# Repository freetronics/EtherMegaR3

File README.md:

Freetronics EtherMega R3
========================
Copyright 2011-2012 Freetronics Pty Ltd  
Freetronics site:  www.freetronics.com  
Freetronics email: info@freetronics.com  

The EtherMega R3 is a 100% Arduino-compatible board based on the existing
Mega2560, but with improvements and updates for features and ease of
use. It also includes on-board Ethernet with PoE (Power-over-Ethernet)
support.

Features:

 * High-efficiency switchmode power supply (input voltage 7-28Vdc)
 * Micro-USB Connector
 * microSD card slot
 * 10/100 Ethernet using the Wiznet W5100 chip
 * Overlay guide where you need it (both top and bottom)
 * D13 pin works for everything

You can view more at our product page at:

  http://www.freetronics.com/ethermega

INSTALLATION
------------
The design is saved as an EAGLE project. EAGLE PCB design software is
available from www.cadsoftusa.com free for non-commercial use. To use
this project download it and place the directory containing these files
into the "eagle" directory on your computer. Then open EAGLE and
navigate to Projects -> eagle -> EtherMegaR3.

DISTRIBUTION
------------
The specific terms of distribution of this project are governed by the
license referenced below.

LICENSE
-------
This work is licensed under the
Creative Commons Attribution-Share Alike License.  
To view a copy of this license, visit

  http://creativecommons.org/licenses/by-sa/3.0/  
  http://creativecommons.org/licenses/by-sa/3.0/legalcode

or send a letter to

  Creative Commons  
  171 Second Street, Suite 300  
  San Francisco  
  California, 94105  
  USA

The "license" folder within this repository also contains copies of the
licences referenced above.

CREDITS
-------
The EtherMega was designed by Marc Alexander (marc@freetronics.com) and
Jonathan Oxer (jon@freetronics.com) based on previous work by the Arduino
team (www.arduino.cc/playground/Main/People) which includes:

 * Massimo Banzi
 * David Cuartielles
 * Tom Igoe
 * Gianluca Martino
 * David A. Mellis

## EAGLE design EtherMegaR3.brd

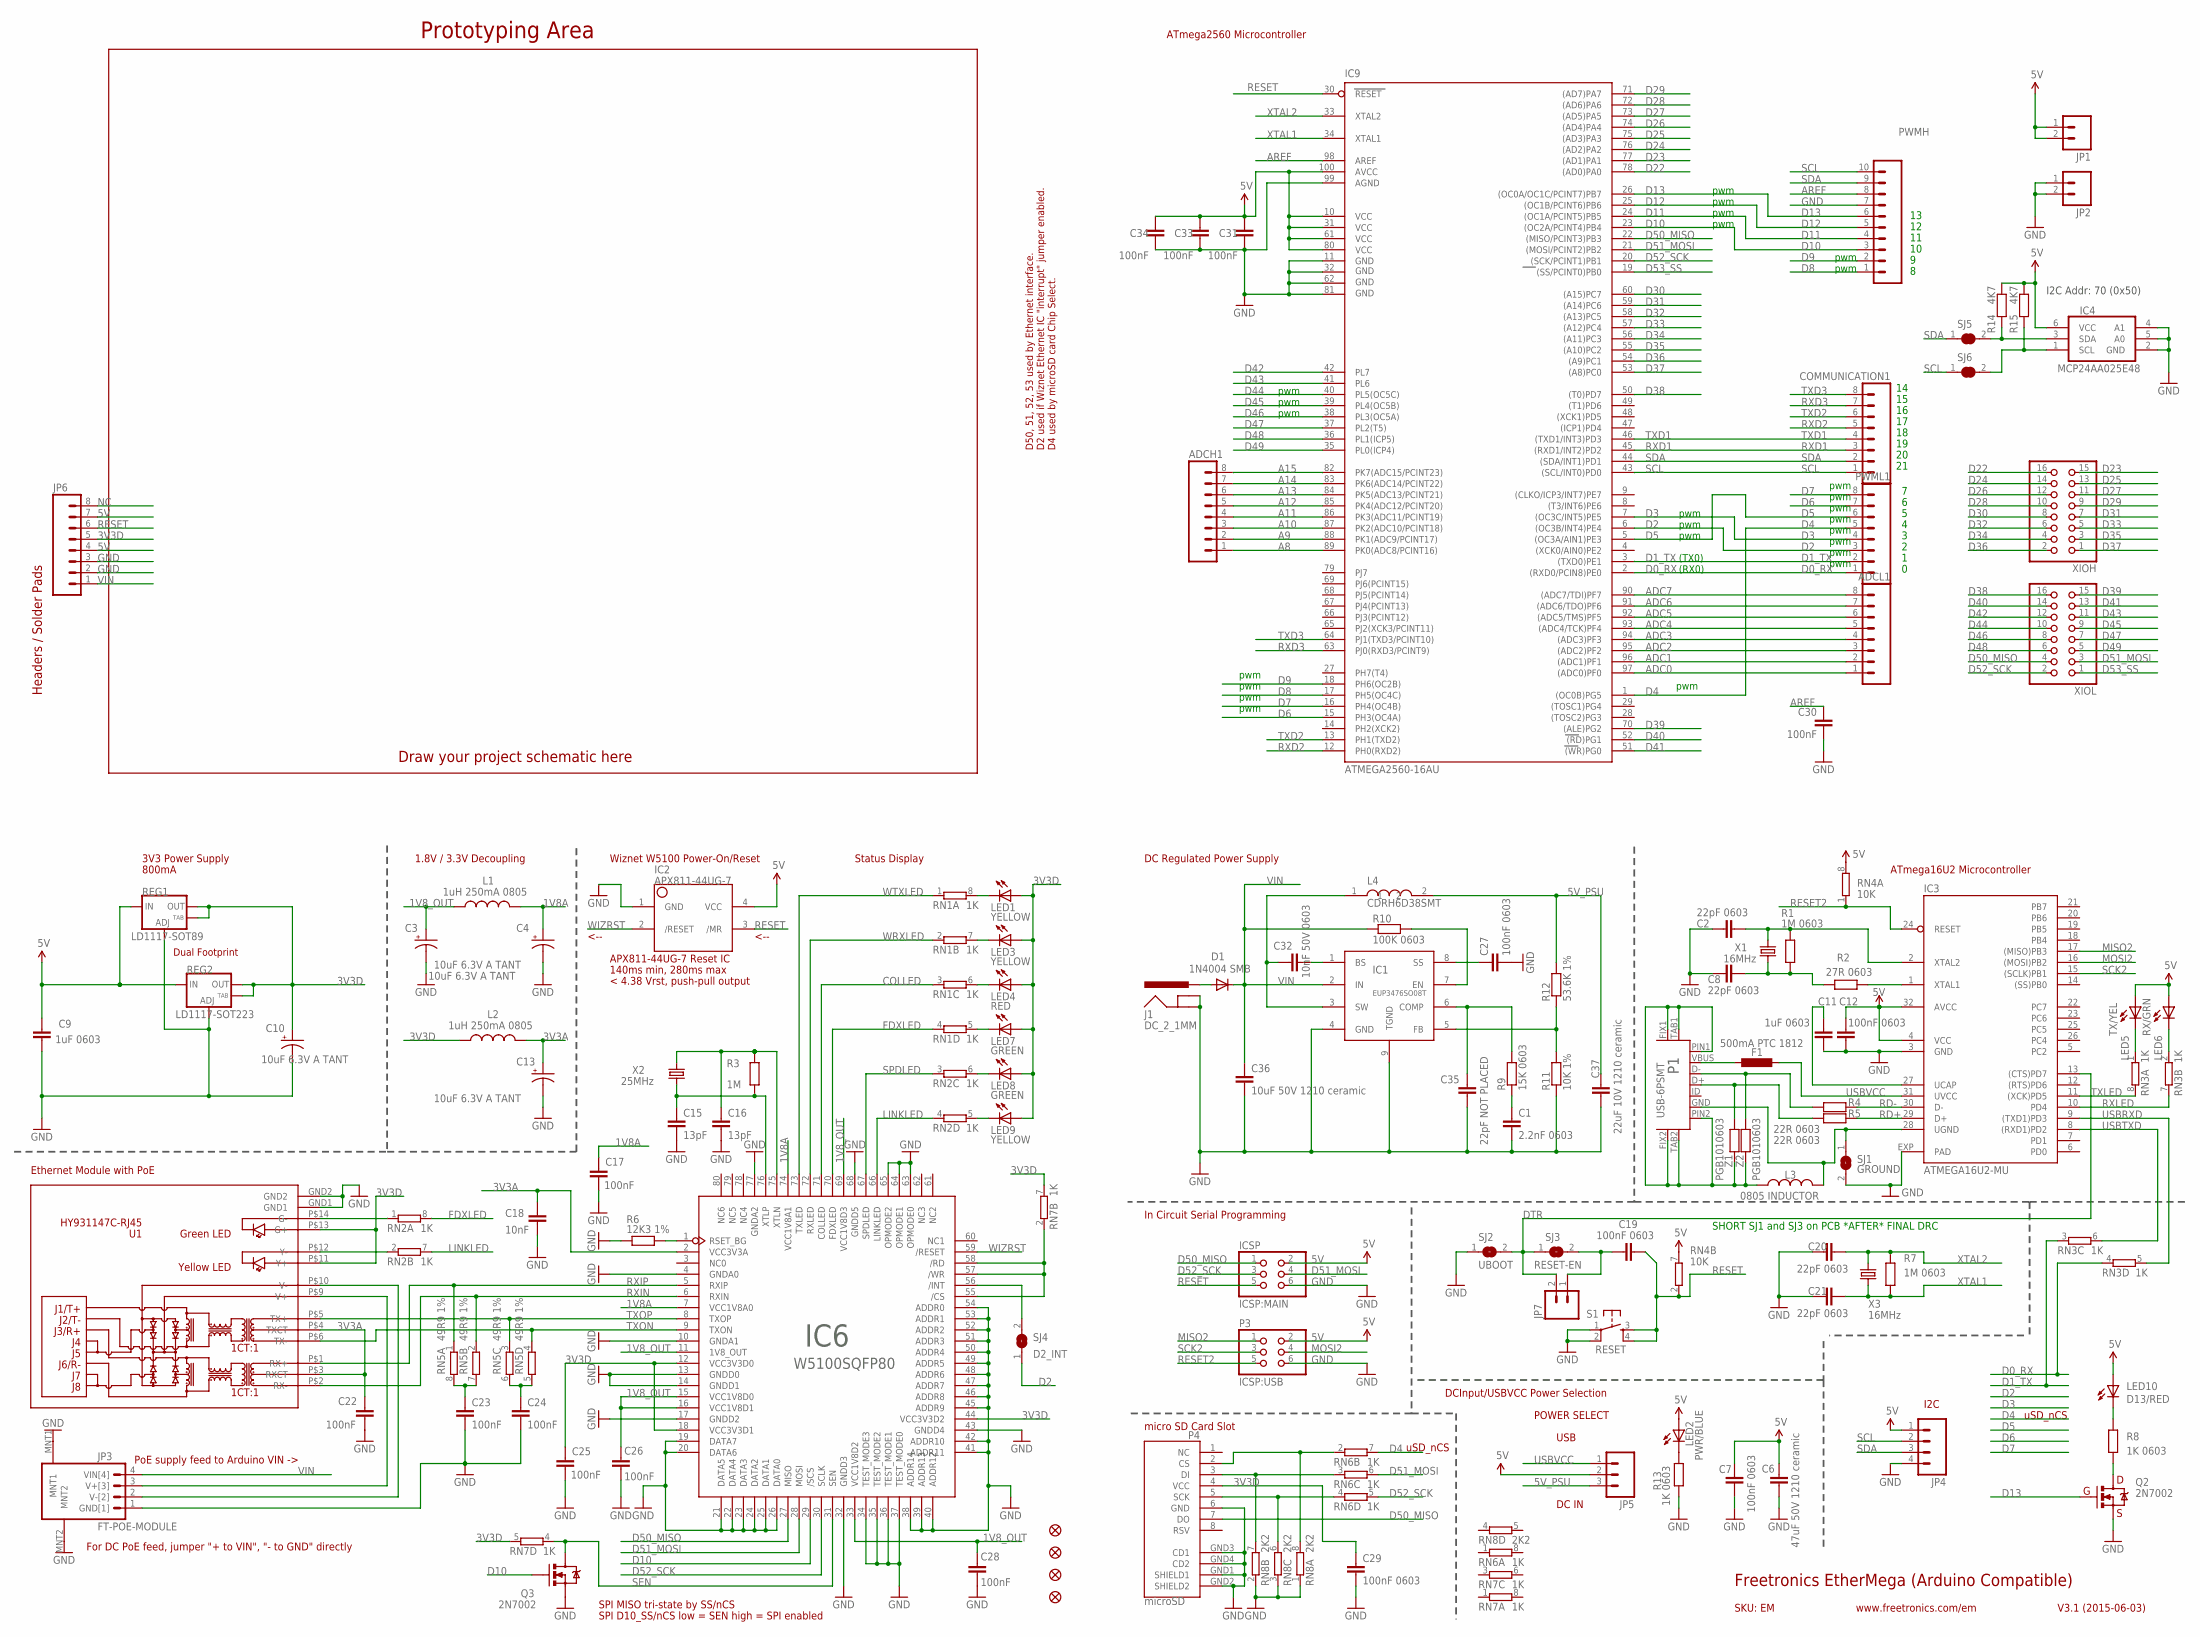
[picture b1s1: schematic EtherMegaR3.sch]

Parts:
ADCH1: M08STD; 1X08
ADCL1: M08STD; 1X08
C1: 2.2nF 0603; 0603
C2, C8, C20, C21: 22pF 0603; 0603
C3, C4, C10, C13: 10uF 6.3V A TANT; EIA3216
C6: 47uF 50V 1210 ceramic; C1210
C7, C12, C19, C27, C29: 100nF 0603; 0603
C9, C11: 1uF 0603; 0603
C15, C16: 13pF; 0603
C17, C22, C23, C24, C25, C26, C28, C30, C31, C33, C34: 100nF; 0603
C18: 10nF; 0603
C32: 10nF 50V 0603; 0603
C35: 22pF NOT PLACED; 0603
C36: 10uF 50V 1210 ceramic; C1210
C37: 22uF 10V 1210 ceramic; C1210
COMMUNICATION1: M08STD; 1X08
D1: 1N4004 SMB; SMB-DIODE
F1: 500mA PTC 1812; L1812
FID1, FID2, FID3, FID4: FIDUCIAL1X2.5; FIDUCIAL-1X2.5
IC1: EUP3476SO08T; SO08T
IC2: APX811-44UG-7; SOT143-R
IC3: ATMEGA16U2-MU; ATMEL_QFN32
IC4: MCP24AA025E48; SOT23-6
IC6: W5100SQFP80; SQFP80
IC9: ATMEGA2560-16AU; TQFP100
ICSP: ICSP:MAIN; 2X03
J1: DC_2_1MM; POWER_JACK_PTH
JP1, JP2, JP7: M02PTH; 1X02
JP3: FT-POE-MODULE; FT-POE-MODULE-CLEAN
JP4: M04PTH; 1X04
JP5: M03PTH; 1X03
JP6: M08STD; 1X08
L1, L2: 1uH 250mA 0805; L2012C
L3: 0805 INDUCTOR; 0805-LARGE
L4: CDRH6D38SMT; CDRH
LED1, LED3, LED9: YELLOW; LED-0603
LED2: PWR/BLUE; LED-0603
LED4: RED; LED-0603
LED5: TX/YEL; LED-0603
LED6: RX/GRN; LED-0603
LED7, LED8: GREEN; LED-0603
LED10: D13/RED; LED-0603
P1: USB-6PSMT; USB-MICROB-MB05PMXX
P3: ICSP:USB; 2X03
P4: microSD; MOLEX-SD-500901-003
PWMH: M100.1; 1X10
PWML1: M08STD; 1X08
Q2, Q3: 2N7002; SOT23-3
R1, R7: 1M 0603; 0603
R2: 27R 0603; 0603
R3: 1M; 0603
R4, R5: 22R 0603; 0603
R6: 12K3 1%; 0603
R8, R13: 1K 0603; 0603
R9: 15K 0603; 0603
R10: 100K 0603; 0603
R11: 10K 1%; 0603
R12: 53.6K 1%; 0603
R14, R15: 4K7; 0603
REG1: LD1117-SOT89; SOT89
REG2: LD1117-SOT223; SOT223
RN1, RN2, RN3, RN6, RN7: 1K; CAY16
RN4: 10K; CAY16
RN5: 49R9 1%; CAY16
RN8: 2K2; CAY16
S1: RESET; TACTILE_SWITCH_SMD
SJ1: GROUND; SJ
SJ2: UBOOT; SJ
SJ3: RESET-EN; SJ
SJ4: D2_INT; SJ
SJ5, SJ6: SJCN; SJC
U1: HY931147C-RJ45; HY931147C
X1, X3: 16MHz; HC49U-V
X2: 25MHz; HC49U-V
XIOH: PINHD-2X8; 2X08
XIOL: PINHD-2X8; 2X08
Z1, Z2: PGB1010603; 0603

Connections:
1V8A: C4.A (+), C17.1, IC6.7 (VCC1V8A0), IC6.74 (VCC1V8A1), L1.2
1V8_OUT: C3.A (+), C26.1, C28.1, IC6.11 (1V8_OUT), IC6.15 (VCC1V8D0), IC6.16 (VCC1V8D1), IC6.33 (VCC1V8D2), IC6.69 (VCC1V8D3), L1.1
3V3A: C13.A (+), C18.1, C22.1, IC6.2 (VCC3V3A), L2.2, U1.P$3 (RXCT), U1.P$4 (TXCT)
3V3D: C10.A (+), C25.1, C29.1, IC6.12 (VCC3V3D0), IC6.18 (VCC3V3D1), IC6.44 (VCC3V3D2), JP6.5, L2.1, LED1.A, LED3.A, LED4.A, LED7.A, LED8.A, LED9.A, P4.4 (VCC), REG1.2 (OUT), REG1.4 (OUT), REG2.2 (OUT), REG2.4 (OUT), RN7.5 (2), RN7.7 (2), U1.P$11 (Y+), U1.P$13 (G+)
5V: C6.2, C7.1, C9.1, C12.1, C31.1, C33.1, C34.1, IC2.4 (VCC), IC3.4 (VCC), IC3.32 (AVCC), IC4.6 (VCC), IC9.10 (VCC), IC9.31 (VCC1), IC9.61 (VCC2), IC9.80 (VCC3), IC9.100 (AVCC), ICSP.2, JP1.1, JP1.2, JP4.1, JP5.2, JP6.4, JP6.7, LED2.A, LED5.A, LED6.A, LED10.A, P3.2, R14.1, R15.1, REG1.3 (IN), REG2.3 (IN), RN4.7 (2), RN4.8 (2)
5V_PSU: C37.1, JP5.3, L4.2, R12.2
A8: ADCH1.1, IC9.89 (PK0(ADC8/PCINT16))
A9: ADCH1.2, IC9.88 (PK1(ADC9/PCINT17))
A10: ADCH1.3, IC9.87 (PK2(ADC10/PCINT18))
A11: ADCH1.4, IC9.86 (PK3(ADC11/PCINT19))
A12: ADCH1.5, IC9.85 (PK4(ADC12/PCINT20))
A13: ADCH1.6, IC9.84 (PK5(ADC13/PCINT21))
A14: ADCH1.7, IC9.83 (PK6(ADC14/PCINT22))
A15: ADCH1.8, IC9.82 (PK7(ADC15/PCINT23))
ADC0: ADCL1.1, IC9.97 ((ADC0)PF0)
ADC1: ADCL1.2, IC9.96 ((ADC1)PF1)
ADC2: ADCL1.3, IC9.95 ((ADC2)PF2)
ADC3: ADCL1.4, IC9.94 ((ADC3)PF3)
ADC4: ADCL1.5, IC9.93 ((ADC4/TCK)PF4)
ADC5: ADCL1.6, IC9.92 ((ADC5/TMS)PF5)
ADC6: ADCL1.7, IC9.91 ((ADC6/TDO)PF6)
ADC7: ADCL1.8, IC9.90 ((ADC7/TDI)PF7)
AREF: C30.1, IC9.98 (AREF), PWMH.8
COLLED: IC6.71 (COLLED), RN1.3 (1)
D0_RX: IC9.2 ((RXD0/PCIN8)PE0), PWML1.1, RN3.4 (1)
D1_TX: IC9.3 ((TXD0)PE1), PWML1.2, RN3.3 (1)
D2: IC9.6 ((OC3B/INT4)PE4), PWML1.3, SJ4.1
D3: IC9.7 ((OC3C/INT5)PE5), PWML1.4
D4: IC9.1 ((OC0B)PG5), PWML1.5, RN6.7 (2)
D5: IC9.5 ((OC3A/AIN1)PE3), PWML1.6
D6: IC9.15 (PH3(OC4A)), PWML1.7
D7: IC9.16 (PH4(OC4B)), PWML1.8
D8: IC9.17 (PH5(OC4C)), PWMH.1
D9: IC9.18 (PH6(OC2B)), PWMH.2
D10: IC6.29 (/SCS), IC9.23 ((OC2A/PCINT4)PB4), PWMH.3, Q3.1 (G)
D11: IC9.24 ((OC1A/PCINT5)PB5), PWMH.4
D12: IC9.25 ((OC1B/PCINT6)PB6), PWMH.5
D13: IC9.26 ((OC0A/OC1C/PCINT7)PB7), PWMH.6, Q2.1 (G)
D22: IC9.78 ((AD0)PA0), XIOH.16
D23: IC9.77 ((AD1)PA1), XIOH.15
D24: IC9.76 ((AD2)PA2), XIOH.14
D25: IC9.75 ((AD3)PA3), XIOH.13
D26: IC9.74 ((AD4)PA4), XIOH.12
D27: IC9.73 ((AD5)PA5), XIOH.11
D28: IC9.72 ((AD6)PA6), XIOH.10
D29: IC9.71 ((AD7)PA7), XIOH.9
D30: IC9.60 ((A15)PC7), XIOH.8
D31: IC9.59 ((A14)PC6), XIOH.7
D32: IC9.58 ((A13)PC5), XIOH.6
D33: IC9.57 ((A12)PC4), XIOH.5
D34: IC9.56 ((A11)PC3), XIOH.4
D35: IC9.55 ((A10)PC2), XIOH.3
D36: IC9.54 ((A9)PC1), XIOH.2
D37: IC9.53 ((A8)PC0), XIOH.1
D38: IC9.50 ((T0)PD7), XIOL.16
D39: IC9.70 ((ALE)PG2), XIOL.15
D40: IC9.52 ((RD)PG1), XIOL.14
D41: IC9.51 ((WR)PG0), XIOL.13
D42: IC9.42 (PL7), XIOL.12
D43: IC9.41 (PL6), XIOL.11
D44: IC9.40 (PL5(OC5C)), XIOL.10
D45: IC9.39 (PL4(OC5B)), XIOL.9
D46: IC9.38 (PL3(OC5A)), XIOL.8
D47: IC9.37 (PL2(T5)), XIOL.7
D48: IC9.36 (PL1(ICP5)), XIOL.6
D49: IC9.35 (PL0(ICP4)), XIOL.5
D50_MISO: IC6.27 (MISO), IC9.22 ((MISO/PCINT3)PB3), ICSP.1, P4.7 (DO), XIOL.4
D51_MOSI: IC6.28 (MOSI), IC9.21 ((MOSI/PCINT2)PB2), ICSP.4, RN6.6 (2), XIOL.3
D52_SCK: IC6.30 (SCLK), IC9.20 ((SCK/PCINT1)PB1), ICSP.3, RN6.5 (2), XIOL.2
D53_SS: IC9.19 ((SS/PCINT0)PB0), XIOL.1
DTR: IC3.13 ((CTS)PD7), JP7.2, SJ2.2, SJ3.1
FDXLED: IC6.70 (FDXLED), RN1.4 (1), RN2.8 (2)
GND: C1.2, C2.1, C3.C (-), C4.C (-), C6.1, C7.2, C8.1, C9.2, C10.C (-), C11.2, C12.2, C13.C (-), C15.2, C16.2, C17.2, C18.2, C20.1, C21.1, C22.2, C23.2, C24.2, C25.2, C26.2, C27.2, C28.2, C29.2, C30.2, C31.2, C33.2, C34.2, C35.2, C36.2, C37.2, IC1.4 (GND), IC1.9 (TGND), IC2.1 (GND), IC3.3 (GND), IC3.EXP (PAD), IC4.2 (GND), IC4.4 (A1), IC4.5 (A0), IC6.4 (GNDA0), IC6.10 (GNDA1), IC6.13 (GNDD0), IC6.14 (GNDD1), IC6.17 (GNDD2), IC6.19 (DATA7), IC6.20 (DATA6), IC6.21 (DATA5), IC6.22 (DATA4), IC6.23 (DATA3), IC6.24 (DATA2), IC6.25 (DATA1), IC6.26 (DATA0), IC6.32 (GNDD3), IC6.34 (TEST_MODE3), IC6.35 (TEST_MODE2), IC6.36 (TEST_MODE1), IC6.37 (TEST_MODE0), IC6.38 (ADDR14), IC6.39 (ADDR13), IC6.40 (ADDR12), IC6.41 (ADDR11), IC6.42 (ADDR10), IC6.43 (GNDD4), IC6.45 (ADDR9), IC6.46 (ADDR8), IC6.47 (ADDR7), IC6.48 (ADDR6), IC6.49 (ADDR5), IC6.50 (ADDR4), IC6.51 (ADDR3), IC6.52 (ADDR2), IC6.53 (ADDR1), IC6.54 (ADDR0), IC6.63 (OPMODE0), IC6.64 (OPMODE1), IC6.65 (OPMODE2), IC6.68 (GNDD5), IC6.77 (GNDA2), IC9.11 (GND), IC9.32 (GND1), IC9.62 (GND2), IC9.81 (GND3), IC9.99 (AGND), ICSP.6, J1.GND, J1.GNDBREAK, JP2.1, JP2.2, JP3.1 (GND[1]), JP3.MNT1, JP3.MNT2, JP4.4, JP6.2, JP6.3, P3.6, P4.6 (GND), P4.GND1 (SHIELD1), P4.GND2 (SHIELD2), P4.GND3 (CD1), P4.GND4 (CD2), PWMH.7, Q2.2 (S), Q3.2 (S), R6.1, R11.1, R13.1, REG1.1 (ADJ), REG2.1 (ADJ), RN8.1, RN8.2 (1), RN8.3 (1), S1.1, S1.2, SJ1.2, SJ2.1, U1.GND1, U1.GND2
LINKLED: IC6.66 (LINKLED), RN2.4 (1), RN2.7 (2)
MISO2: IC3.17 ((MISO)PB3), P3.1
MOSI2: IC3.16 ((MOSI)PB2), P3.4
unnamed: C24.1, RN5.5 (2), RN5.6 (2)
unnamed: LED10.C, R8.2
unnamed: Q2.3 (D), R8.1
unnamed: IC3.1 (XTAL1), R2.1
unnamed: IC4.1 (SCL), R15.2, SJ6.2
unnamed: LED6.C, RN3.2 (1)
unnamed: LED2.C, R13.2
unnamed: LED5.C, RN3.1
unnamed: P1.D+, R5.2, Z1.1
unnamed: P1.D-, R4.2, Z2.1
unnamed: L3.1, P1.FIX1, P1.FIX2, P1.PIN1, P1.PIN2, P1.TAB1, P1.TAB2, Z1.2, Z2.2
unnamed: IC4.3 (SDA), R14.2, SJ5.2
unnamed: P4.5 (SCK), RN6.4 (1), RN8.6 (2)
unnamed: P4.2 (CS), RN6.2 (1), RN8.8 (2)
unnamed: P4.3 (DI), RN6.3 (1), RN8.7 (2)
unnamed: LED8.C, RN2.6 (2)
unnamed: IC6.55 (/CS), IC6.57 (/WR), IC6.58 (/RD), RN7.2 (1)
unnamed: LED9.C, RN2.5 (2)
unnamed: D1.A, J1.PWR
unnamed: IC6.56 (/INT), SJ4.2
unnamed: C27.1, IC1.8 (SS)
unnamed: C1.1, R9.1
unnamed: C35.1, IC1.6 (COMP), R9.2
unnamed: RN2.1, U1.P$14 (G-)
unnamed: JP3.3 (V+[3]), U1.P$9 (V+)
unnamed: JP3.2 (V-[2]), U1.P$10 (V-)
unnamed: C32.1, IC1.3 (SW), L4.1
unnamed: C32.2, IC1.1 (BS)
unnamed: IC1.7 (EN), R10.2
unnamed: IC3.28 (UGND), L3.2, P1.GND, SJ1.1
unnamed: C19.1, JP7.1, SJ3.2
unnamed: IC1.5 (FB), R11.2, R12.1
unnamed: C2.2, IC3.2 (XTAL2), R1.2, X1.2
unnamed: C8.2, R1.1, R2.2, X1.1
unnamed: F1.1, P1.VBUS
unnamed: C11.1, IC3.27 (UCAP)
unnamed: C23.1, RN5.7 (2), RN5.8 (2)
unnamed: IC6.1 (RSET_BG), R6.2
unnamed: LED7.C, RN1.5 (2)
unnamed: LED4.C, RN1.6 (2)
unnamed: LED3.C, RN1.7 (2)
unnamed: LED1.C, RN1.8 (2)
unnamed: RN2.2 (1), U1.P$12 (Y-)
NC: JP6.8
RD+: IC3.29 (D+), R5.1
RD-: IC3.30 (D-), R4.1
RESET: C19.2, IC2.3 (/MR), IC9.30 (RESET), ICSP.5, JP6.6, RN4.2 (1), S1.3, S1.4
RESET2: IC3.24 (RESET), P3.5, RN4.1
RXD1: COMMUNICATION1.3, IC9.45 ((RXD1/INT2)PD2)
RXD2: COMMUNICATION1.5, IC9.12 (PH0(RXD2))
RXD3: COMMUNICATION1.7, IC9.63 (PJ0(RXD3/PCINT9))
RXIN: IC6.6 (RXIN), RN5.2 (1), U1.P$2 (RX-)
RXIP: IC6.5 (RXIP), RN5.1, U1.P$1 (RX+)
RXLED: IC3.10 (PD4), RN3.7 (2)
SCK2: IC3.15 ((SCLK)PB1), P3.3
SCL: COMMUNICATION1.1, IC9.43 ((SCL/INT0)PD0), JP4.2, PWMH.10, SJ6.1
SDA: COMMUNICATION1.2, IC9.44 ((SDA/INT1)PD1), JP4.3, PWMH.9, SJ5.1
SEN: IC6.31 (SEN), Q3.3 (D), RN7.4 (1)
SPDLED: IC6.67 (SPDLED), RN2.3 (1)
TXD1: COMMUNICATION1.4, IC9.46 ((TXD1/INT3)PD3)
TXD2: COMMUNICATION1.6, IC9.13 (PH1(TXD2))
TXD3: COMMUNICATION1.8, IC9.64 (PJ1(TXD3/PCINT10))
TXLED: IC3.11 ((XCK)PD5), RN3.8 (2)
TXON: IC6.9 (TXON), RN5.4 (1), U1.P$6 (TX-)
TXOP: IC6.8 (TXOP), RN5.3 (1), U1.P$5 (TX+)
USBRXD: IC3.9 ((TXD1)PD3), RN3.5 (2)
USBTXD: IC3.8 ((RXD1)PD2), RN3.6 (2)
USBVCC: F1.2, IC3.31 (UVCC), JP5.1
VIN: C36.1, D1.C, IC1.2 (IN), JP3.4 (VIN[4]), JP6.1, R10.1
WIZRST: IC2.2 (/RESET), IC6.59 (/RESET)
WRXLED: IC6.72 (RXLED), RN1.2 (1)
WTXLED: IC6.73 (TXLED), RN1.1
XTAL1: C21.2, IC9.34 (XTAL1), R7.1, X3.1
XTAL2: C20.2, IC9.33 (XTAL2), R7.2, X3.2
XTLN: C16.1, IC6.75 (XTLN), R3.2, X2.2
XTLP: C15.1, IC6.76 (XTLP), R3.1, X2.1

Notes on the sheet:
Prototyping Area
3V3 Power Supply
Status Display
Headers / Solder Pads
Dual Footprint
1.8V / 3.3V Decoupling
Draw your project schematic here
D50, 51, 52, 53 used by Ethernet interface.
D2 used if Wiznet Ethernet IC "interrupt" jumper enabled.
PoE supply feed to Arduino VIN ->
SPI MISO tri-state by SS/nCS
SPI D10_SS/nCS low = SEN high = SPI enabled
For DC PoE feed, jumper "+ to VIN", "- to GND" directly
DC Regulated Power Supply
ATmega2560 Microcontroller
APX811-44UG-7 Reset IC
140ms min, 280ms max
ATmega16U2 Microcontroller
DCInput/USBVCC Power Selection
Wiznet W5100 Power-On/Reset
uSD_nCS
800mA
In Circuit Serial Programming
micro SD Card Slot
Freetronics EtherMega (Arduino Compatible)
V3.1 (2015-06-03)
www.freetronics.com/em
SKU: EM
Ethernet Module with PoE
< 4.38 Vrst, push-pull output
<--
D4 used by microSD card Chip Select.
pwm
(TX0)
(RX0)
SHORT SJ1 and SJ3 on PCB *AFTER* FINAL DRC
I2C
USB
DC IN
POWER SELECT

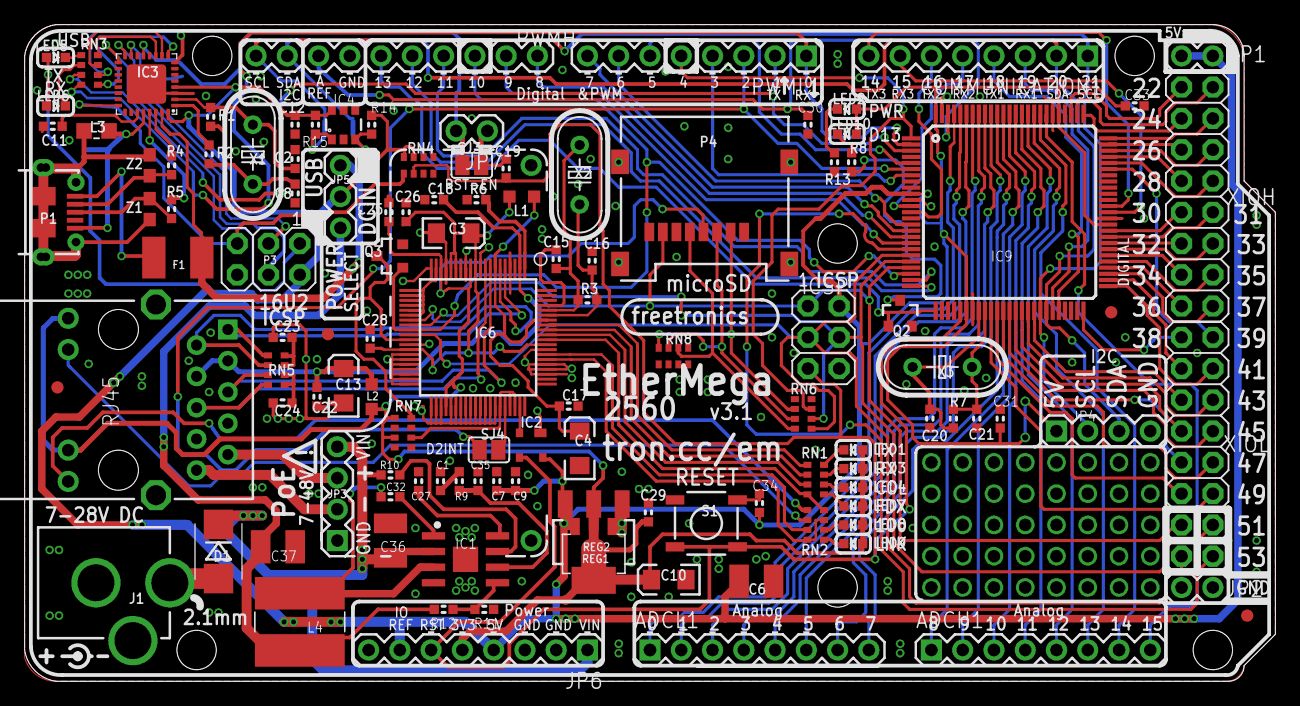
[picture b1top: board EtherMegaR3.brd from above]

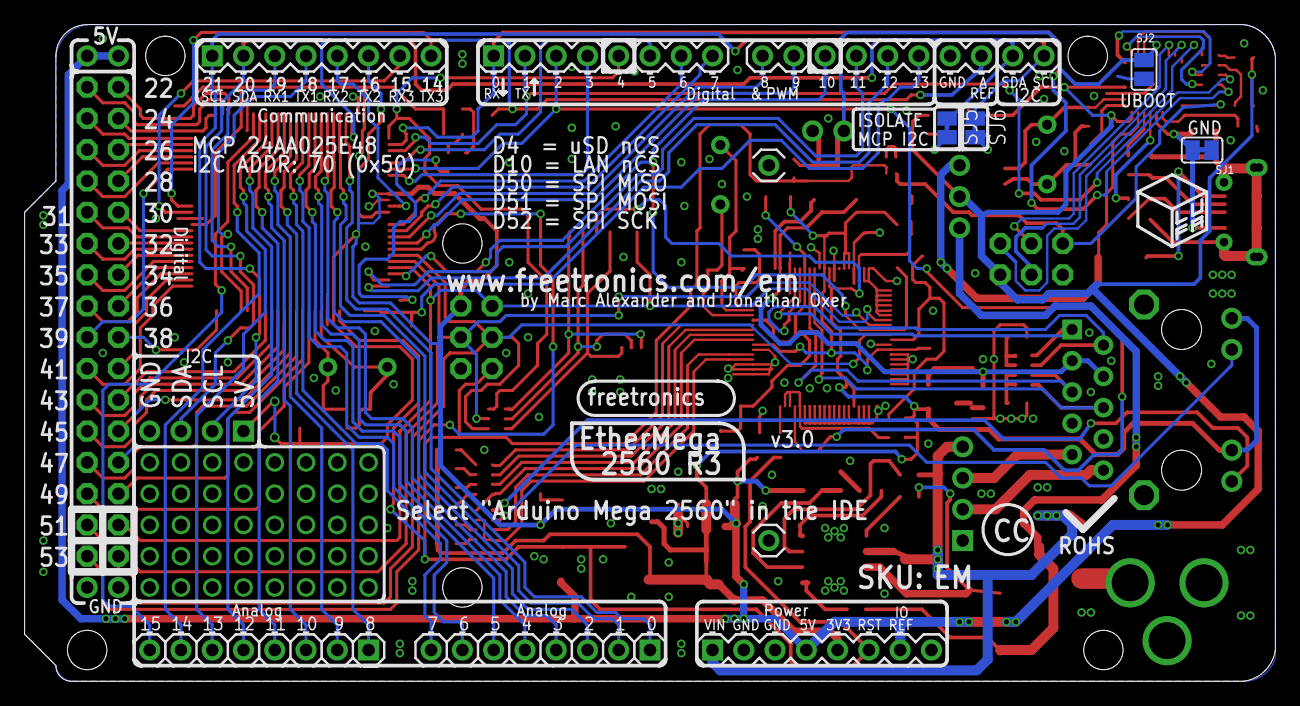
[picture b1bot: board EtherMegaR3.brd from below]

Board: 2 copper layers, 101.6 x 53.3 mm, 120 parts (4 on the bottom side), 151 nets.

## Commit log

2011-05-14 Initial project files
2011-05-14 Cleaned up some net names
2011-05-15 Routing
2011-05-18 Updated net names; routing
2011-05-28 Making a mess
2011-06-13 Pushin and shovin
2011-07-06 Fixed split SPI problem; more routing
2011-07-12 Changed PWR LED dropper to 2k2; routing
2011-07-18 Net name fix, SJ short-jumpers cleaned
2011-07-24 Added I2C header, plus more routing
2011-08-15 Started replacing linear reg with switcher
2011-08-30 Replaced linear regulator with switcher
2011-08-30 Minor schematic rearrangement
2011-09-05 Routing switchmode supply
2011-09-08 Routing updates
2011-09-09 Routing tweaks
2011-09-12 Clearance adjustments
2011-09-16 Minor schematic cleanup
2011-09-16 DRC clearances
2011-09-17 Overlay and routing tweaks
2011-09-17 Silkscreen tweaks
2011-09-17 Clearances
2011-09-17 Shorted SJ1 and SJ3 for production
2011-09-17 Changed references to pins reserved for SPI
2011-09-17 Tiny silkscreen fixes
2011-09-19 Improved part name placement
2011-10-04 Removed power autoswitcher
2011-10-07 Jumper selection of power source
2011-10-09 Jumper power source USBVCC in progress
2011-10-09 USB and DC-IN power selection, DRC passed
2011-10-10 Updated EUP3476 footprint
2011-10-10 ERC's and power ports sorted out
2011-10-11 v1.0 release!
    Tons'o'tweaks, All DRC's gone through, 8U2 GND fixed, Overlays, PWR LED R and cleanup
2011-10-11 v1.0 release, C35 and R9 value revision
2011-10-25 Changed Wiznet SS from D53 to D10
2011-10-26 Minor overlay update for v1.1 release
2011-10-26 Overlay updates for v1.1 release
2011-10-26 Changed R12 to 53K6 to fix vreg output
2011-10-26 v1.1 production release
2011-12-06 Added CC license text
2012-07-09 Renamed files for R3 revision
2012-07-09 Swapped headers
2012-07-09 Project name change in README
2012-08-18 Changes for R3 release
2013-08-29 Added MAC address chip and changed to hinge SD socket for v3.0 release
2015-03-22 Added v3.0 schematic
2015-06-03 Added M02 header in parallel with RST-EN cut-track link for external reset mode control
